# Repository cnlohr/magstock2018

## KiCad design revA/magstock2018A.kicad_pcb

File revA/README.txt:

* 1.6mm LEAD-FREE
* GREEN PCBS
* The WS2813s have PIN1 pointing DOWN and to the RIGHT.
* Molex 0.1" Connectors may be replaced with any kind.
* TLV70036 regulator may be replaced with any 3.6V regulator.
* D5 (DO-214AB Schottky) Must be at least 20V, and at rated to least 4A.  Must be DO-214AB or similar size.
* ONLY SOURCE ESP12E from ELECTRODRAGON.
* TACTILE switches should be full-size tactile switches, used on first MAGFest order.
* Microphone should be through-hole electret microphone.
* 3.5mm Barrel Jack should be similar to Digikey P/N CP-3536N-ND.
* TLV70036 regulator may be replaced with any 3.6v regulator with similar pinout and 350mA and max in voltage of 6V.

"Id";"Designator";"Package";"Quantity";"Designation";"Supplier and ref";
3;"C1,C4";"R_0805";2;".1u10v";;;
4;"C2";"R_0805";1;"1u10v";;;
6;"C5,C6";"R_0805";2;"10u10v";;;
7;"ESP1";"ESP12E";1;"ESP12E";;;
8;"J3";"Molex_KK-6410-04_04x2.54mm_Straight";1;"WS2813";;;
9;"MK1";"CP_Radial_D10.0mm_P2.50mm_P5.00mm";1;"Microphone";;;
10;"R1,R13";"R_0805";2;"47k";;;
11;"R2,R3,R5";"R_0805";3;"4k7";;;
12;"R4,R11";"R_0805";2;"10k";;;
13;"U1,U2";"SOT-23-5_HandSoldering";2;"TLV70036";;;
14;"D1,D2,D3,D4,D6,D7,D8,D9";"WS2813";8;"WS2813";;;
15;"SW1,SW2,SW3,SW4,SW5,SW6";"TACTILE10";6;"TACTILE";;;
16;"J2";"PJ-037A";1;"5vdcIn";;;
17;"P1";"USB_Micro-B_10103594-0001LF";1;"USBMicroB-10118194-0001LF";;;
18;"D5";"DO-214AB";1;"Schottky";;;
19;"R6";"R_0805";1;"1.5k";;;
21;"J4";"Molex_KK-6410-05_05x2.54mm_Straight";1;"Conn_01x05";;;
22;"J1";"3.5mm_barrel_jack_MJ-3536N";1;"Conn_01x03";;;
23;"R10";"R_0805";1;"220k";;;
24;"R12";"R_0805";1;"22k";;;
25;"U3";"SOT-23-5";1;"OPAMP_MCP6001T";;;
26;"C7";"R_0805";1;"10u";;;

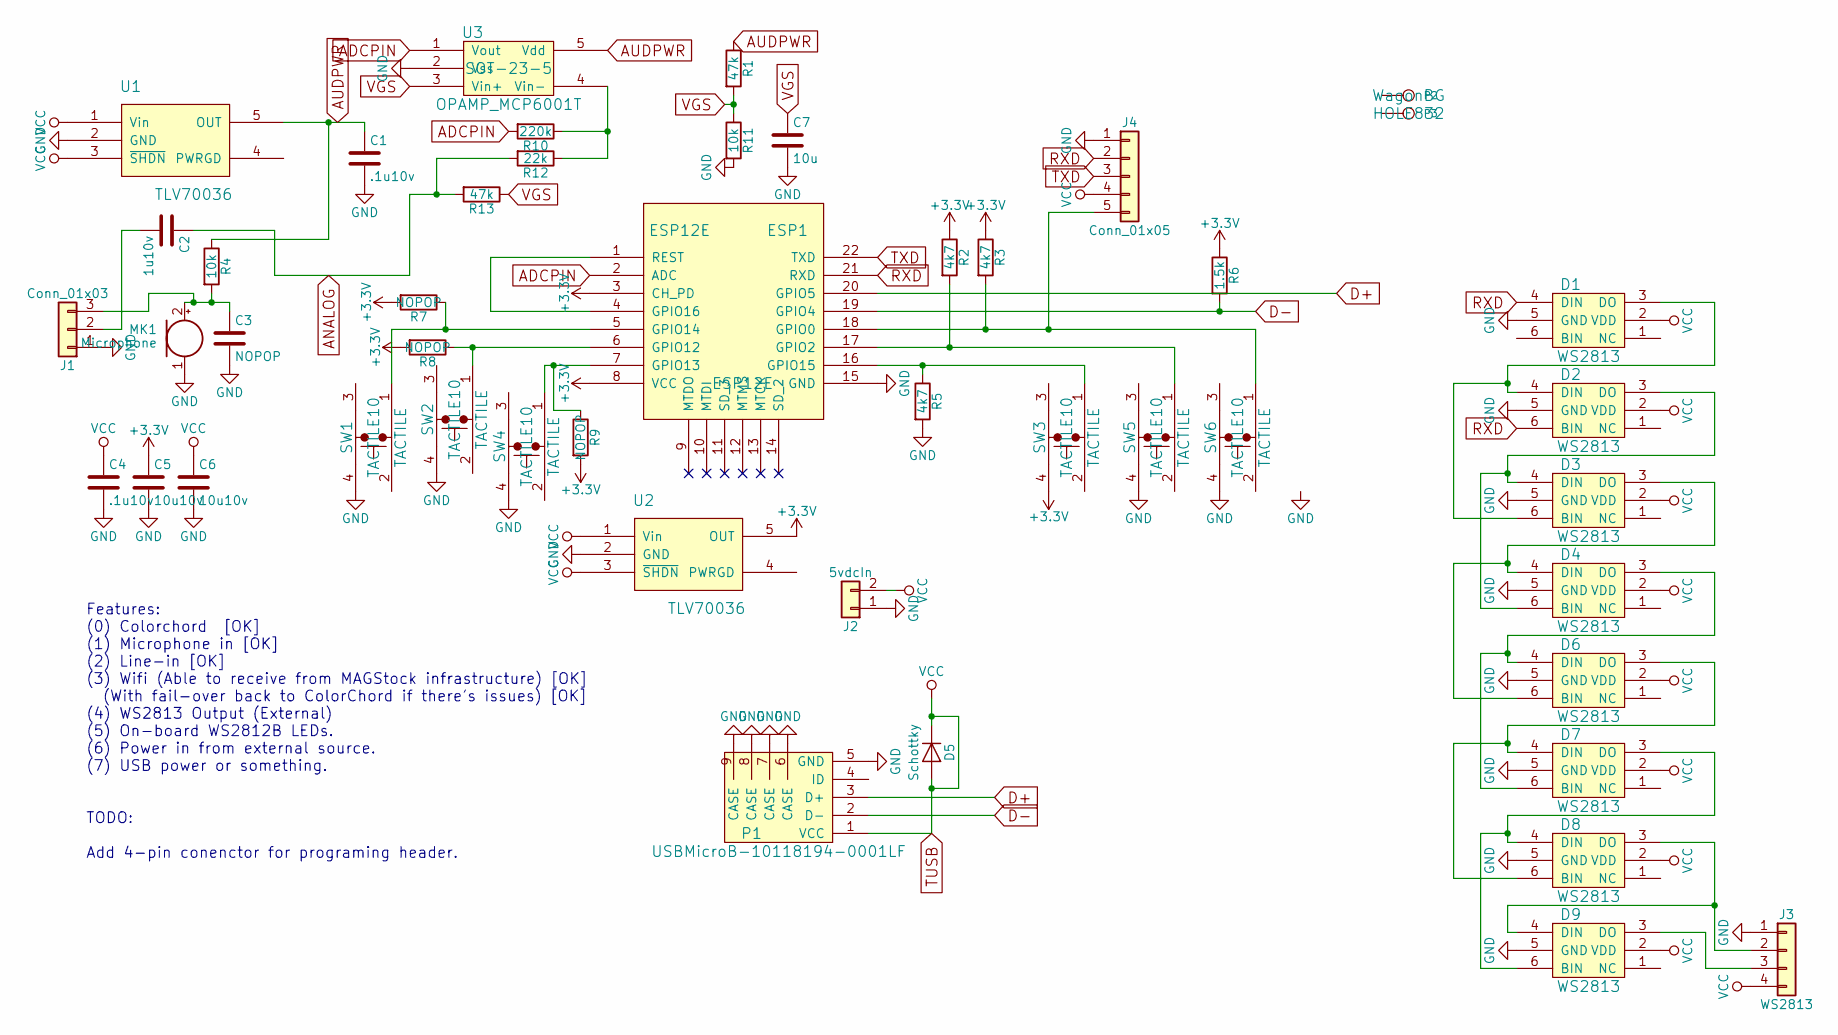
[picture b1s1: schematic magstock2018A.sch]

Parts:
C1, C4: .1u10v; R_0805
C2: 1u10v; R_0805
C3: NOPOP; R_0805
C5, C6: 10u10v; R_0805
C7: 10u; R_0805
D1, D2, D3, D4, D6, D7, D8, D9: WS2813
D5: Schottky; DO-214AB; Digikey SK36A R3GCT-ND
ESP1: ESP12E
J1: Conn_01x03; 3.5mm_barrel_jack_MJ-3536N; Digikey CP-3536N-ND
J2: 5vdcIn; PJ-037A; Digikey CP-037A-ND
J3: WS2813; Molex_KK-6410-04_04x2.54mm_Straight
J4: Conn_01x05; Molex_KK-6410-05_05x2.54mm_Straight
MK1: Microphone; CP_Radial_D10.0mm_P2.50mm_P5.00mm; Digikey 668-1460-ND
P1: USBMicroB-10118194-0001LF; USB_Micro-B_10103594-0001LF; Digikey 609-4050-1-ND
P2: CONN_1; WagonBG
P3: CONN_1; HOLE832
R1, R13: 47k; R_0805
R2, R3, R5: 4k7; R_0805
R4, R11: 10k; R_0805
R6: 1.5k; R_0805
R7, R8, R9: NOPOP; R_0805
R10: 220k; R_0805
R12: 22k; R_0805
SW1, SW2, SW3, SW4, SW5, SW6: TACTILE; TACTILE10; Digikey CKN9112CT-ND
U1, U2: TLV70036; SOT-23-5_HandSoldering; Digikey 296-40611-1-ND
U3: OPAMP_MCP6001T; SOT-23-5; Digikey MCP6001UT-I/OTCT-ND

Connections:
+3V3: C5.1, ESP1.3 (CH_PD), ESP1.8 (VCC), R2.1, R3.1, R6.1, R7.2, R8.2, R9.2, SW3.4, U2.5 (OUT)
ADCPIN: ESP1.2 (ADC), R10.2, U3.1 (Vout)
ANALOG: C2.1, R12.2, R13.2
AUDPWR: C1.1, R1.1, R4.1, U1.5 (OUT), U3.5 (Vdd)
D+: ESP1.20 (GPIO5), P1.3 (D+)
D-: ESP1.19 (GPIO4), P1.2 (D-), R6.2
GND: C1.2, C3.2, C4.2, C5.2, C6.2, C7.2, D1.5 (GND), D2.5 (GND), D3.5 (GND), D4.5 (GND), D6.5 (GND), D7.5 (GND), D8.5 (GND), D9.5 (GND), ESP1.15 (GND), J1.1, J2.1, J3.1, J4.1, MK1.1 (-), P1.5 (GND), P1.6 (CASE), P1.7 (CASE), P1.8 (CASE), P1.9 (CASE), R5.2, R11.2, SW1.4, SW2.4, SW4.4, SW5.4, SW6.4, U1.2 (GND), U2.2 (GND), U3.2 (Vss)
unnamed: C2.2, J1.2
unnamed: C3.1, J1.3, MK1.2 (+), R4.2
unnamed: D1.3 (DO), D2.4 (DIN), D3.6 (BIN)
unnamed: D2.3 (DO), D3.4 (DIN), D4.6 (BIN)
unnamed: D3.3 (DO), D4.4 (DIN), D6.6 (BIN)
unnamed: D4.3 (DO), D6.4 (DIN), D7.6 (BIN)
unnamed: D6.3 (DO), D7.4 (DIN), D8.6 (BIN)
unnamed: D7.3 (DO), D8.4 (DIN), D9.6 (BIN)
unnamed: D8.3 (DO), D9.4 (DIN), J3.2
unnamed: D9.3 (DO), J3.3
unnamed: ESP1.1 (REST), ESP1.4 (GPIO16)
unnamed: ESP1.5 (GPIO14), R7.1, SW1.1
unnamed: ESP1.6 (GPIO12), R8.1, SW2.1
unnamed: ESP1.7 (GPIO13), R9.1, SW4.1
unnamed: ESP1.16 (GPIO15), R5.1, SW3.1
unnamed: ESP1.17 (GPIO2), R2.2, SW5.1
unnamed: ESP1.18 (GPIO0), J4.5, R3.2, SW6.1
unnamed: R10.1, R12.1, U3.4 (Vin-)
RXD: D1.4 (DIN), D2.6 (BIN), ESP1.21 (RXD), J4.2
TUSB: C4.1, C6.1, D1.2 (VDD), D2.2 (VDD), D3.2 (VDD), D4.2 (VDD), D5.1 (K), D5.2 (A), D6.2 (VDD), D7.2 (VDD), D8.2 (VDD), D9.2 (VDD), J2.2, J3.4, J4.4, P1.1 (VCC), U1.1 (Vin), U1.3 (~SHDN), U2.1 (Vin), U2.3 (~SHDN)
TXD: ESP1.22 (TXD), J4.3
VGS: C7.1, R1.2, R11.1, R13.1, U3.3 (Vin+)

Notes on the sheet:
Features: (0) Colorchord [OK] (1) Microphone in [OK] (2) Line-in [OK] (3) Wifi (Able to receive from MAGStock infrastructure) [OK] (With fail-over back to ColorChord if there's issues) [OK] (4) WS2813 Output (External) (5) On-board WS2812B LEDs. (6) Power in from external source. (7) USB power or s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

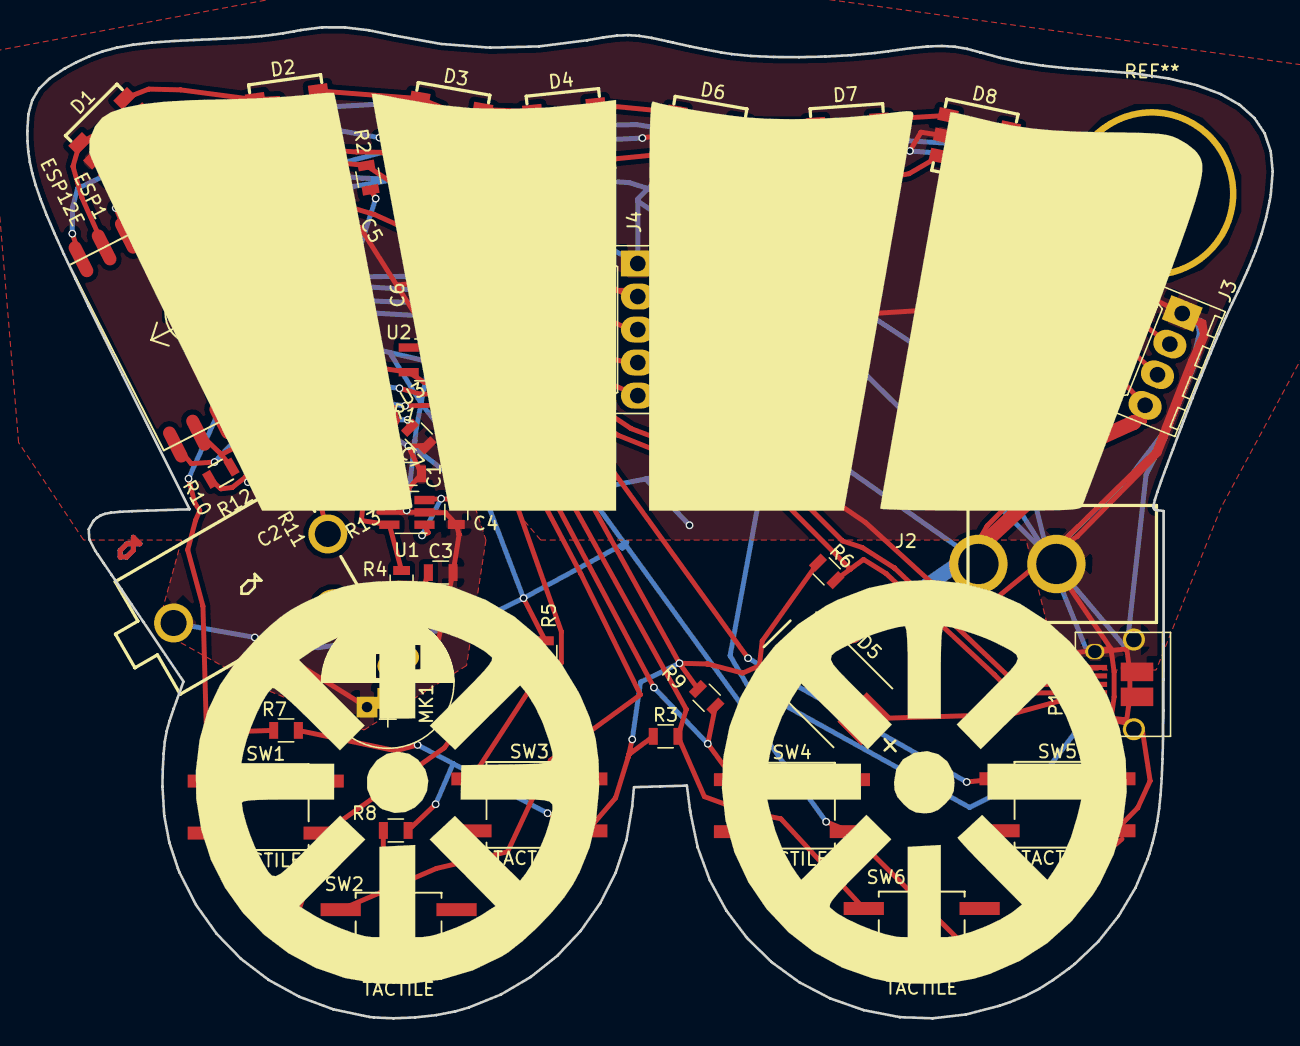
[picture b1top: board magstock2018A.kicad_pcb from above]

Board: 2 copper layers, 95.8 x 76.2 mm, 46 parts (0 on the bottom side), 29 nets.

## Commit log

2018-03-25 Commit to github.
2018-03-27 Update files
2018-03-27 Update reva
2018-03-28 Updates!
2018-03-28 Update!
2018-03-28 Butmp
2018-04-11 Update to rev b.
2018-04-12 Update to optional revc
2018-04-19 bump
2018-04-20 Bump everything
2018-04-28 Bump rev D
2018-04-28 Bump rev zip
2018-05-04 push extra wire bridge
2018-05-04 bump rev
2018-05-04 Add D5 note
2018-06-06 Add firmware
2018-06-06 Add readme
2018-06-06 bump firmware
2018-06-06 add binaries
2018-06-06 add embeddedcommon
2018-06-07 bump to new SDK
2018-06-07 Bump all
2018-06-07 trying here
2018-06-07 Update code with new swadge stuff
2018-06-07 Add missing parts.
2018-06-07 bump submodule
2018-06-07 Added binaries
2018-06-07 WORKING
2018-06-07 almost there
2018-06-07 Yay! RC1
2018-06-07 pass
2018-06-07 Allow monitoring of colors
2018-06-07 bump new firmware?
2018-06-07 bump improve flashlight
2018-07-22 add image.elf
2018-07-22 update images
